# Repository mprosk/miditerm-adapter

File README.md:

# MidiTerm USB Adapter
MIDI UART to USB adapter designed for use with the [`miditerm`](https://github.com/mprosk/miditerm) application.

This is simply the MIDI electrical interface connected to an FTDI UART to USB Serial IC. It allows you to connect to MIDI devices as a USB serial port rather than as a class compliant USB MIDI device, allowing for lower level access to the individual data bytes.

I had a broken Yamaha Model UX16 USB-MIDI Interface cable lying around so I decided to design the board to fit into the enclosure within that cable. It opens easily and has the cables nicely exposed so it was super easy to hack into. Thanks Yamaha

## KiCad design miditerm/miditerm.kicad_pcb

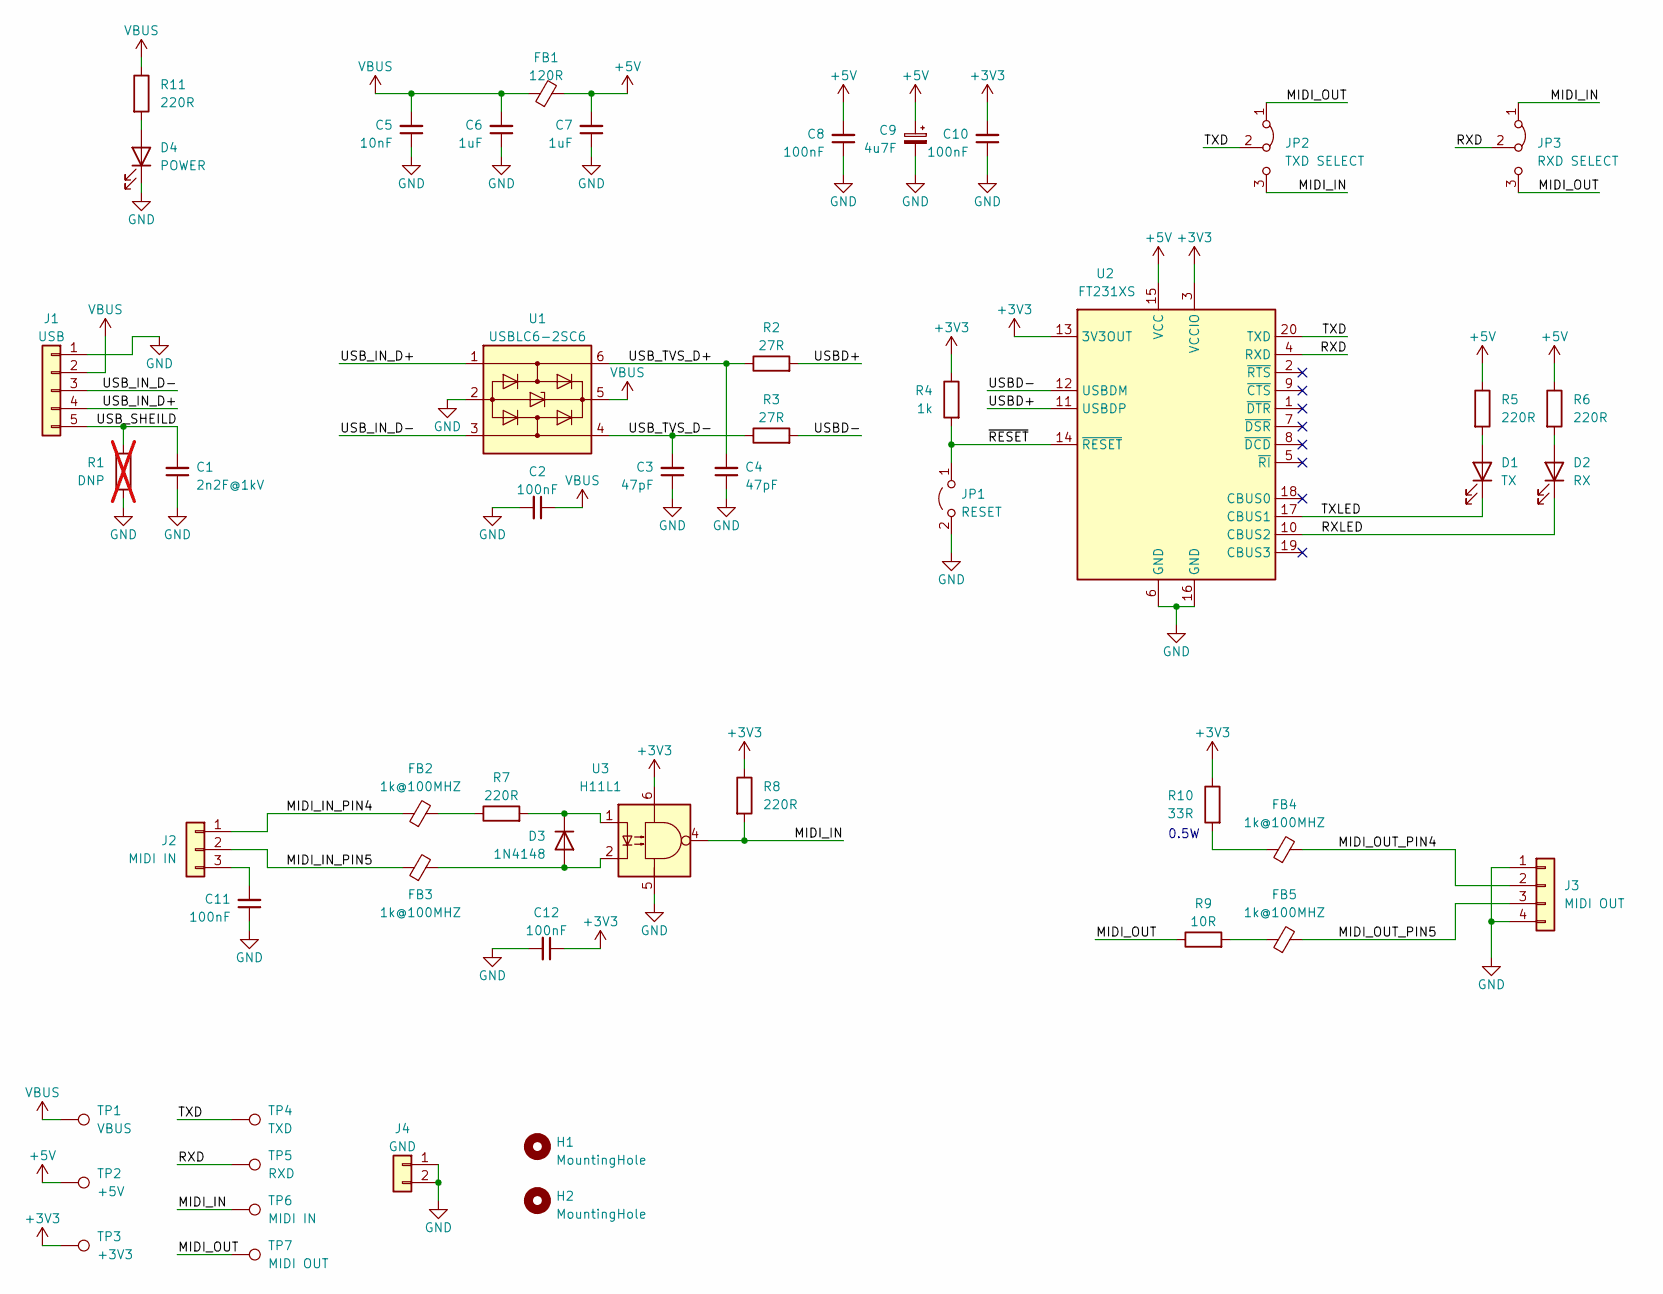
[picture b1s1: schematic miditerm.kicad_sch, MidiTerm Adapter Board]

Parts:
C1: 2n2F@1kV; C_0805_2012Metric
C2, C8, C10, C11, C12: 100nF; C_0805_2012Metric
C3, C4: 47pF; C_0805_2012Metric
C5: 10nF; C_0805_2012Metric
C6, C7: 1uF; C_0805_2012Metric
C9: 4u7F; CP_Radial_D5.0mm_P2.00mm
D1: TX; LED_D3.0mm
D2: RX; LED_D3.0mm
D3: 1N4148; D_SOD-123
D4: POWER; LED_D3.0mm
FB1: 120R; L_0805_2012Metric
FB2, FB3, FB4, FB5: 1k@100MHZ; L_0805_2012Metric
H1, H2: MountingHole; MountingHole_2.2mm_M2
J1: USB; PinHeader_1x05_P2.00mm_Vertical
J2: MIDI IN; PinHeader_1x03_P2.00mm_Vertical
J3: MIDI OUT; PinHeader_1x04_P2.00mm_Vertical
J4: GND; PinHeader_1x02_P2.54mm_Vertical
JP1: RESET; SolderJumper-2_P1.3mm_Open_Pad1.0x1.5mm
JP2: TXD SELECT; SolderJumper-3_P1.3mm_Bridged12_RoundedPad1.0x1.5mm
JP3: RXD SELECT; SolderJumper-3_P1.3mm_Bridged12_RoundedPad1.0x1.5mm
R1: DNP; R_0805_2012Metric; not fitted
R2, R3: 27R; R_0805_2012Metric
R4: 1k; R_0805_2012Metric
R5, R6, R7, R8, R11: 220R; R_0805_2012Metric
R9: 10R; R_0805_2012Metric
R10: 33R; R_0805_2012Metric
TP1: VBUS; TestPoint_Pad_D1.5mm
TP2: +5V; TestPoint_Pad_D1.5mm
TP3: +3V3; TestPoint_Pad_D1.5mm
TP4: TXD; TestPoint_Pad_D1.5mm
TP5: RXD; TestPoint_Pad_D1.5mm
TP6: MIDI IN; TestPoint_Pad_D1.5mm
TP7: MIDI OUT; TestPoint_Pad_D1.5mm
U1: USBLC6-2SC6; SOT-23-6
U2: FT231XS; SSOP-20_3.9x8.7mm_P0.635mm
U3: H11L1; SMDIP-6_W9.53mm

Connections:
+3V3: C10.2, C12.1, R4.1, R8.1, R10.1, TP3.1, U2.3 (VCCIO), U2.13 (3V3OUT), U3.6
+5V: C7.2, C8.2, C9.1, FB1.2, R5.1, R6.1, TP2.1, U2.15 (VCC)
/MIDI_IN: JP2.3 (B), JP3.1 (A), R8.2, TP6.1, U3.4
/MIDI_IN_PIN4: FB2.1, J2.1
/MIDI_IN_PIN5: FB3.1, J2.2
/MIDI_OUT: JP2.1 (A), JP3.3 (B), R9.1, TP7.1
/MIDI_OUT_PIN4: FB4.2, J3.2
/MIDI_OUT_PIN5: FB5.2, J3.3
/RXD: JP3.2 (C), TP5.1, U2.4 (RXD)
/RXLED: D2.1 (K), U2.10 (CBUS2)
/TXD: JP2.2 (C), TP4.1, U2.20 (TXD)
/TXLED: D1.1 (K), U2.17 (CBUS1)
/USBD+: R2.2, U2.11 (USBDP)
/USBD-: R3.2, U2.12 (USBDM)
/USB_IN_D+: J1.4, U1.1 (I/O1)
/USB_IN_D-: J1.3, U1.3 (I/O2)
/USB_SHEILD: C1.2, J1.5, R1.1
/USB_TVS_D+: C4.2, R2.1, U1.6 (I/O1)
/USB_TVS_D-: C3.2, R3.1, U1.4 (I/O2)
/~RESET: JP1.1 (A), R4.2, U2.14 (~RESET)
GND: C1.1, C2.2, C3.1, C4.1, C5.1, C6.1, C7.1, C8.1, C9.2, C10.1, C11.1, C12.2, D4.1 (K), J1.1, J3.1, J3.4, J4.1, J4.2, JP1.2 (B), R1.2, U1.2 (GND), U2.6 (GND), U2.16 (GND), U3.5
unnamed: D1.2 (A), R5.2
unnamed: D2.2 (A), R6.2
unnamed: D3.2 (A), FB3.2, U3.2
unnamed: D3.1 (K), R7.2, U3.1
unnamed: D4.2 (A), R11.2
unnamed: FB2.2, R7.1
unnamed: FB4.1, R10.2
unnamed: FB5.1, R9.2
unnamed: C11.2, J2.3
VBUS: C2.1, C5.2, C6.2, FB1.1, J1.2, R11.1, TP1.1, U1.5 (VBUS)

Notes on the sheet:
0.5W

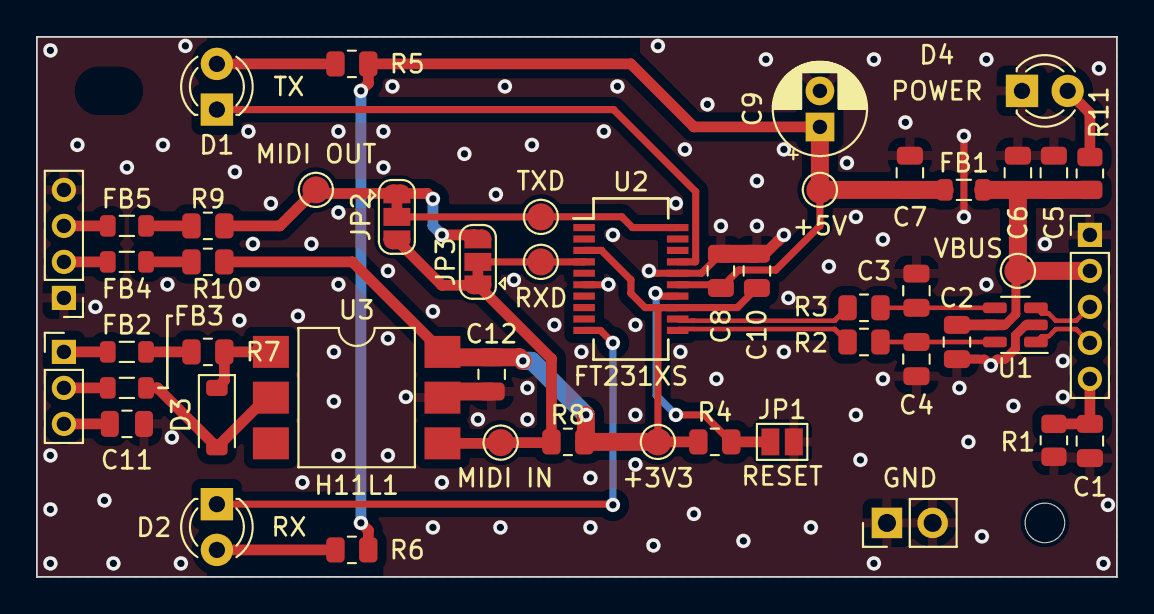
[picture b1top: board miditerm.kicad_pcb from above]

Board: 2 copper layers, 60.0 x 30.0 mm, 51 parts (0 on the bottom side), 31 nets.

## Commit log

2023-03-31 Complete PCB design
2023-03-31 Cleanup
2023-04-07 Update resistor values for LEDs
